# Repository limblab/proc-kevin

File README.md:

# proc-kevin
Kevin's analysis code

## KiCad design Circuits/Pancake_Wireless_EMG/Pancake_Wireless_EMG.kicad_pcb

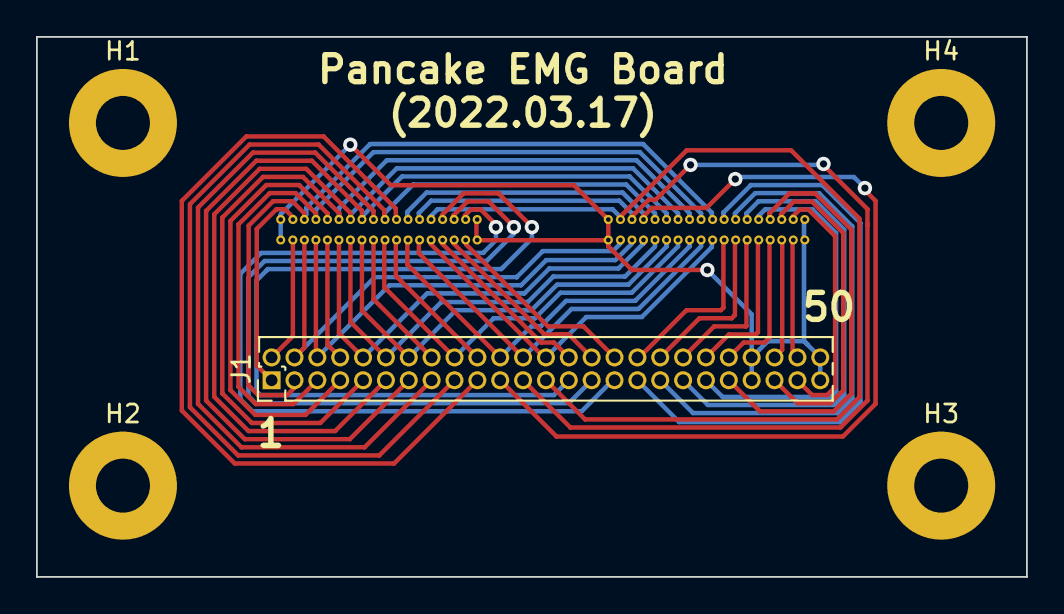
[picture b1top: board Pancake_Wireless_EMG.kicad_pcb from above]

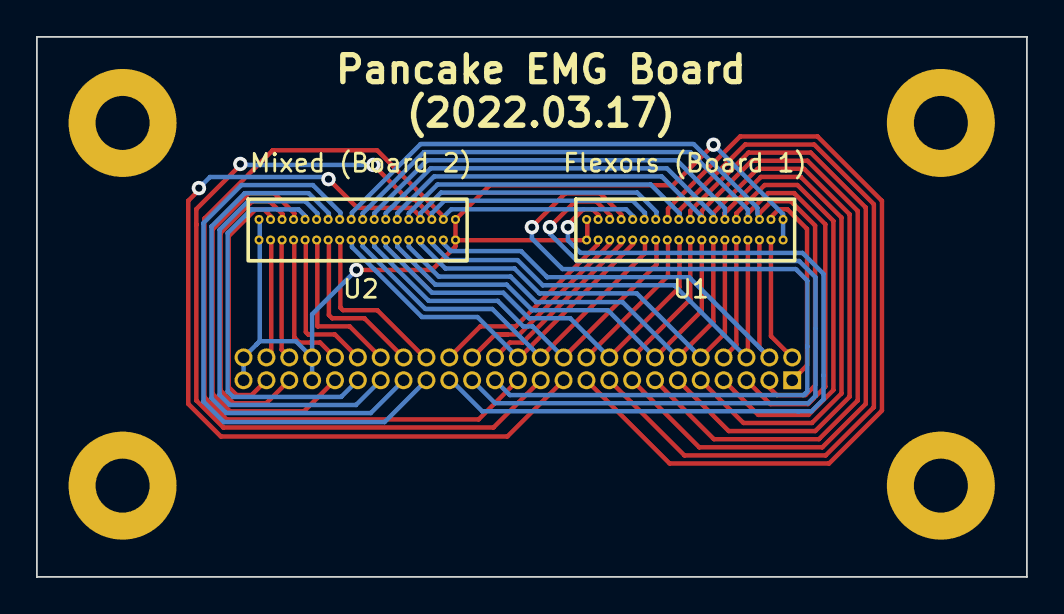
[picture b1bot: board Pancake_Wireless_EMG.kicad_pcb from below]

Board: 2 copper layers, 55.0 x 30.0 mm, 7 parts (2 on the bottom side), 47 nets.

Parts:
H1, H2, H3, H4: MountingHole; MountingHole_3mm_Pad
J1: Conn_02x25_Odd_Even; PinHeader_2x25_P1.27mm_Vertical
U1, U2: Omnetics_A79026; Omnetics_A97022

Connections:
/1DI_1: J1.27, U1.27 (In26)
/1DI_2: J1.28, U1.22 (In21)
/3DI_1: J1.31, U1.25 (In24)
/3DI_2: J1.32, U1.24 (In23)
/APB_1: J1.19, U1.31 (In30)
/APB_2: J1.20, U1.18 (In17)
/Bi_1: J1.47, U2.25 (In24)
/Bi_2: J1.48, U2.24 (In23)
/ECR_1: J1.36, U2.19 (In18)
/ECR_2: J1.37, U2.29 (In28)
/ECR_3: J1.38, U2.20 (In19)
/ECU_1: J1.33, U2.31 (In30)
/ECU_2: J1.34, U2.18 (In17)
/ECU_3: J1.35, U2.30 (In29)
/EDC1_1: J1.39, U2.28 (In27)
/EDC1_2: J1.40, U2.21 (In20)
/EDC2_1: J1.41, U2.27 (In26)
/EDC2_2: J1.42, U2.22 (In21)
/EPL_1: J1.25, U1.28 (In27), U2.8 (In7)
/EPL_2: J1.26, U1.21 (In20), U2.17 (In16)
/FCR1_1: J1.1, U1.8 (In7)
/FCR1_2: J1.2, U1.9 (In8)
/FCR2_1: J1.3, U1.7 (In6), U2.32 (In31)
/FCR2_2: J1.4, U1.10 (In9), U2.9 (In8)
/FCU1_1: J1.5, U1.6 (In5), U2.1 (In0)
/FCU1_2: J1.6, U1.11 (In10), U2.10 (In9)
/FCU2_1: J1.7, U1.5 (In4)
/FCU2_2: J1.8, U1.12 (In11)
/FDP1_1: J1.9, U1.4 (In3), U2.2 (In1)
/FDP1_2: J1.10, U1.13 (In12), U2.11 (In10)
/FDP2_1: J1.11, U1.3 (In2), U2.3 (In2)
/FDP2_2: J1.12, U1.14 (In13), U2.12 (In11)
/FDS1_1: J1.13, U1.2 (In1), U2.4 (In3)
/FDS1_2: J1.14, U1.15 (In14), U2.13 (In12)
/FDS2_1: J1.15, U1.1 (In0)
/FDS2_2: J1.16, U1.16 (In15)
/FPB_1: J1.21, U1.30 (In29), U2.6 (In5)
/FPB_2: J1.22, U1.19 (In18), U2.15 (In14)
/Gnd: J1.43, J1.44, J1.49, J1.50, U1.33 (GND), U1.34 (REF), U1.35 (REF), U1.36 (GND), U2.33 (GND), U2.34 (REF), U2.35 (REF), U2.36 (GND)
/Lum_1: J1.23, U1.29 (In28), U2.7 (In6)
/Lum_2: J1.24, U1.20 (In19), U2.16 (In15)
/PT_1: J1.17, U1.32 (In31), U2.5 (In4)
/PT_2: J1.18, U1.17 (In16), U2.14 (In13)
/Sup_1: J1.29, U1.26 (In25)
/Sup_2: J1.30, U1.23 (In22)
/Tri_1: J1.45, U2.26 (In25)
/Tri_2: J1.46, U2.23 (In22)

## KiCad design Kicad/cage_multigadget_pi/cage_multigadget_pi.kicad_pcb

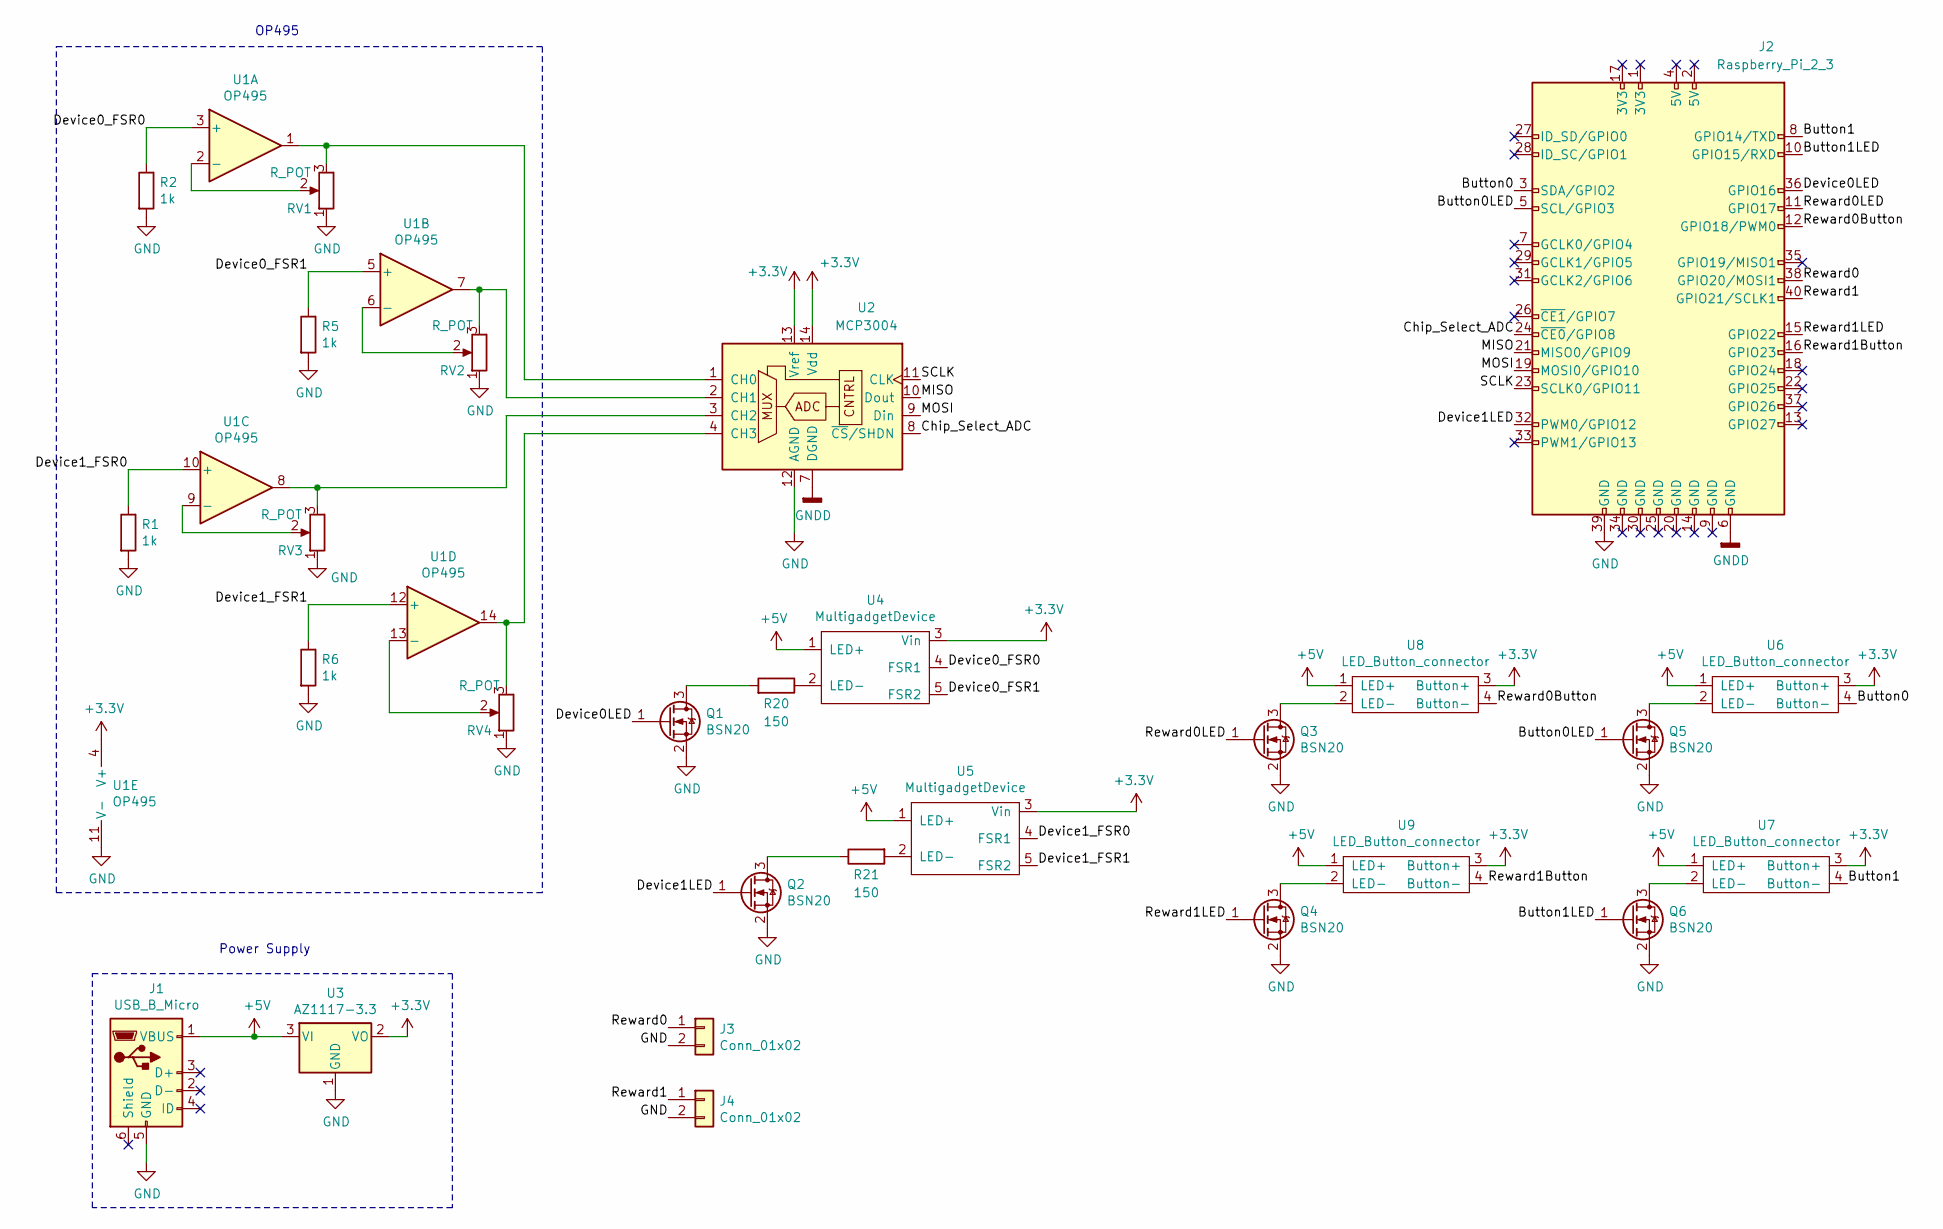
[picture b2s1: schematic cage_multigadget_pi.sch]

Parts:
J1: USB_B_Micro; USB_Micro_B_Female_10118194-0001LF
J2: Raspberry_Pi_2_3; Pin_Header_Straight_2x20_Pitch2.54mm
J3, J4: Conn_01x02; Socket_Strip_Straight_1x02_Pitch2.54mm
Q1, Q2, Q3, Q4, Q5, Q6: BSN20; SOT-23
R1, R2, R5, R6: 1k; R_1206_3216Metric_Pad1.42x1.75mm_HandSolder
R20, R21: 150; R_1206_3216Metric_Pad1.42x1.75mm_HandSolder
RV1, RV2, RV3, RV4: R_POT; Potentiometer_Trimmer_Bourns_3296Y
U1: OP495; DIP-14_W7.62mm
U2: MCP3004; DIP-14_W7.62mm
U3: AZ1117-3.3; SOT-223
U4, U5: MultigadgetDevice; CUI_MD-80S
U6, U7, U8, U9: LED_Button_connector; CUI_MD-80S

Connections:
+3V3: U1.4 (V+), U2.13 (Vref), U2.14 (Vdd), U3.2 (VO), U4.3 (Vin), U5.3 (Vin), U6.3 (Button+), U7.3 (Button+), U8.3 (Button+), U9.3 (Button+)
+5V: J1.1 (VBUS), U3.3 (VI), U4.1 (LED+), U5.1 (LED+), U6.1 (LED+), U7.1 (LED+), U8.1 (LED+), U9.1 (LED+)
/Button0: J2.3 (SDA/GPIO2), U6.4 (Button-)
/Button0LED: J2.5 (SCL/GPIO3), Q5.1 (G)
/Button1: J2.8 (GPIO14/TXD), U7.4 (Button-)
/Button1LED: J2.10 (GPIO15/RXD), Q6.1 (G)
/Chip_Select_ADC: J2.24 (~CE0~/GPIO8), U2.8 (~CS~/SHDN)
/Device0LED: J2.36 (GPIO16), Q1.1 (G)
/Device0_FSR0: R2.1, U1.3 (+), U4.4 (FSR1)
/Device0_FSR1: R5.1, U1.5 (+), U4.5 (FSR2)
/Device1LED: J2.32 (PWM0/GPIO12), Q2.1 (G)
/Device1_FSR0: R1.1, U1.10 (+), U5.4 (FSR1)
/Device1_FSR1: R6.1, U1.12 (+), U5.5 (FSR2)
/MISO: J2.21 (MISO0/GPIO9), U2.10 (Dout)
/MOSI: J2.19 (MOSI0/GPIO10), U2.9 (Din)
/Reward0: J2.38 (GPIO20/MOSI1), J3.1
/Reward0Button: J2.12 (GPIO18/PWM0), U8.4 (Button-)
/Reward0LED: J2.11 (GPIO17), Q3.1 (G)
/Reward1: J2.40 (GPIO21/SCLK1), J4.1
/Reward1Button: J2.16 (GPIO23), U9.4 (Button-)
/Reward1LED: J2.15 (GPIO22), Q4.1 (G)
/SCLK: J2.23 (SCLK0/GPIO11), U2.11 (CLK)
GND: J1.5 (GND), J2.39 (GND), J3.2, J4.2, Q1.2 (S), Q2.2 (S), Q3.2 (S), Q4.2 (S), Q5.2 (S), Q6.2 (S), R1.2, R2.2, R5.2, R6.2, RV1.1, RV2.1, RV3.1, RV4.1, U1.11 (V-), U2.12 (AGND), U3.1 (GND)
GNDD: J2.6 (GND), U2.7 (DGND)
unnamed: Q1.3 (D), R20.2
unnamed: Q2.3 (D), R21.1
unnamed: Q3.3 (D), U8.2 (LED-)
unnamed: Q4.3 (D), U9.2 (LED-)
unnamed: Q5.3 (D), U6.2 (LED-)
unnamed: Q6.3 (D), U7.2 (LED-)
unnamed: R20.1, U4.2 (LED-)
unnamed: R21.2, U5.2 (LED-)
unnamed: RV1.2, U1.2 (-)
unnamed: RV1.3, U1.1, U2.1 (CH0)
unnamed: RV2.2, U1.6 (-)
unnamed: RV2.3, U1.7, U2.2 (CH1)
unnamed: RV3.2, U1.9 (-)
unnamed: RV3.3, U1.8, U2.3 (CH2)
unnamed: RV4.2, U1.13 (-)
unnamed: RV4.3, U1.14, U2.4 (CH3)

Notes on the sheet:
Power Supply
OP495

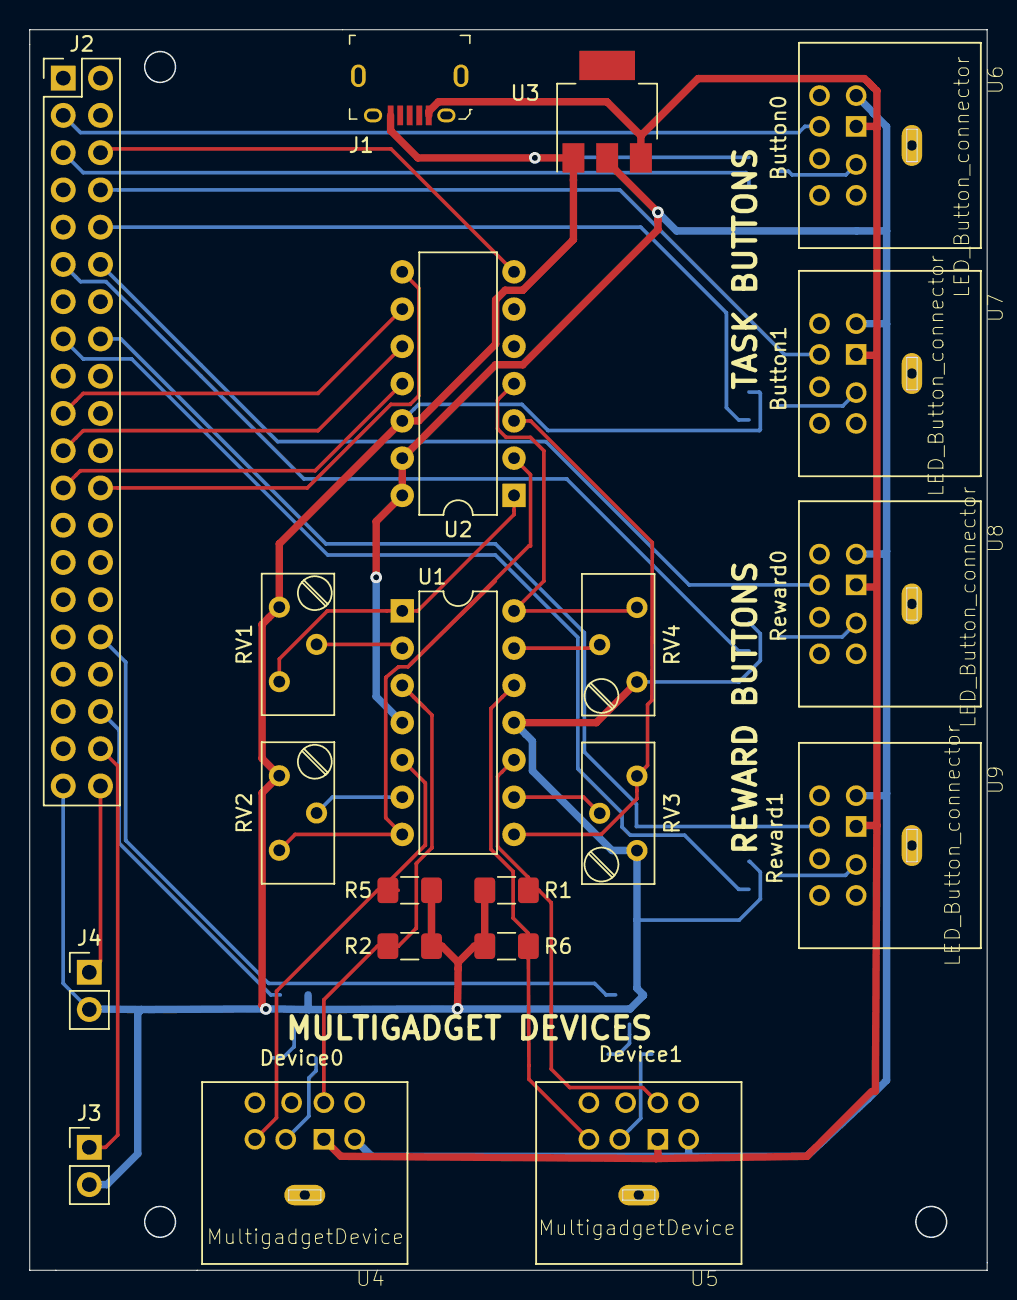
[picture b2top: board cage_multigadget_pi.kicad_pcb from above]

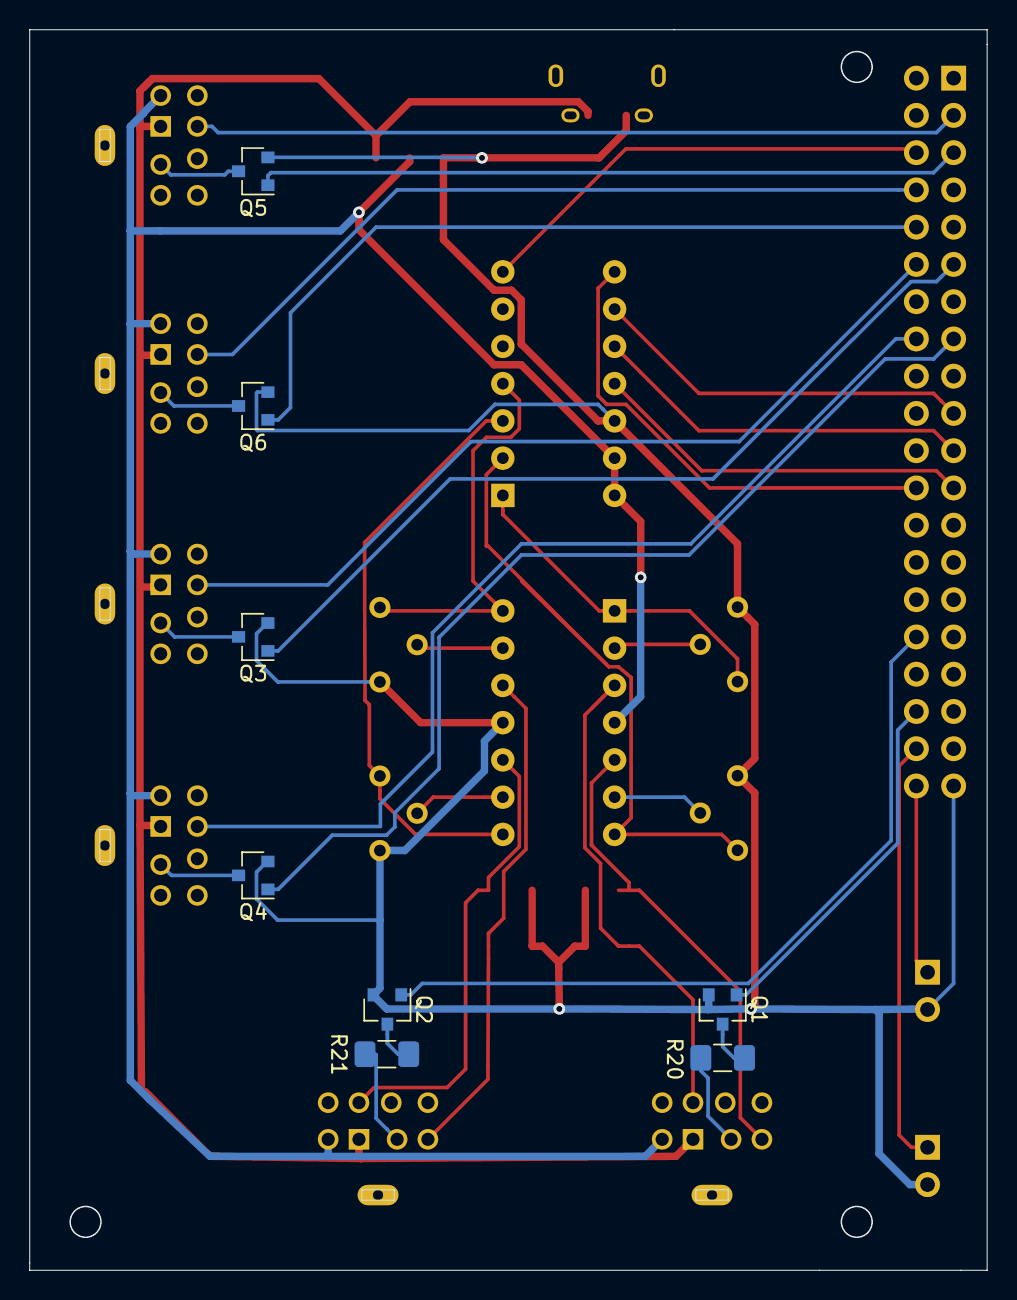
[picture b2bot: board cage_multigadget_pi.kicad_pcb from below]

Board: 2 copper layers, 65.3 x 84.6 mm, 29 parts (8 on the bottom side), 40 nets.

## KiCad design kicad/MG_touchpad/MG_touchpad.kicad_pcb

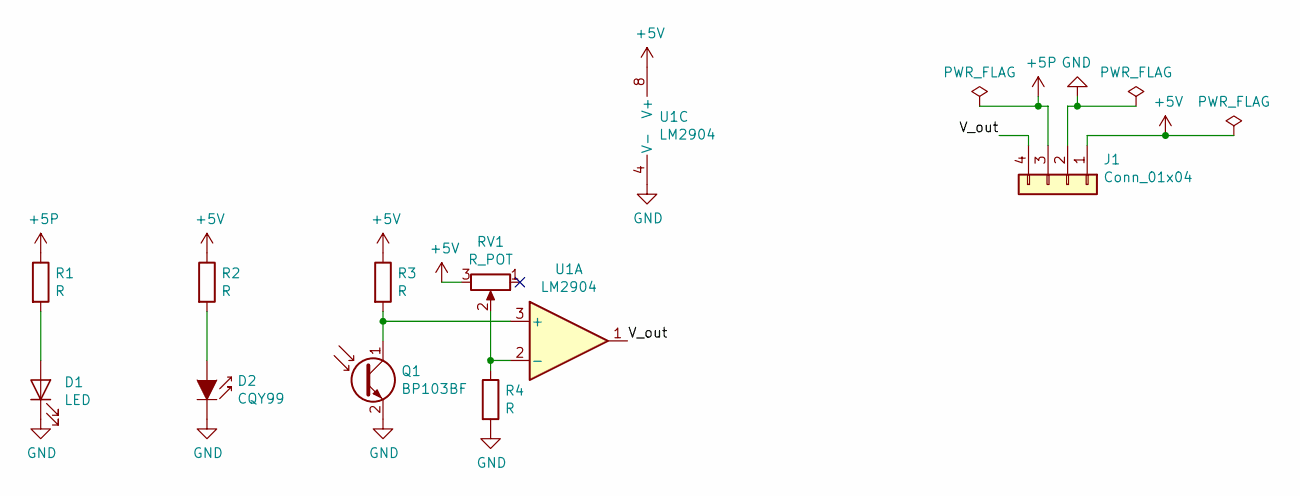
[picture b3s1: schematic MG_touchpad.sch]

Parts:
D1: LED; JST_PH_B2B-PH-K_02x2.00mm_Straight
D2: CQY99; JST_PH_B2B-PH-K_02x2.00mm_Straight
J1: Conn_01x04; Pin_Header_Angled_1x04_Pitch2.54mm
Q1: BP103BF; JST_PH_B2B-PH-K_02x2.00mm_Straight
R1, R2, R3, R4: R; R_1206
RV1: R_POT; Potentiometer_Trimmer_Bourns_3296Y
U1: LM2904; DIP-8_W7.62mm

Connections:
+5P: J1.3, R1.1
+5V: J1.1, R2.1, R3.1, RV1.3, U1.8 (V+)
/V_out: J1.4, U1.1
GND: D1.1 (K), D2.1 (K), J1.2, Q1.2 (E), R4.2, U1.4 (V-)
unnamed: D1.2 (A), R1.2
unnamed: D2.2 (A), R2.2
unnamed: Q1.1 (C), R3.2, U1.3 (+)
unnamed: R4.1, RV1.2, U1.2 (-)

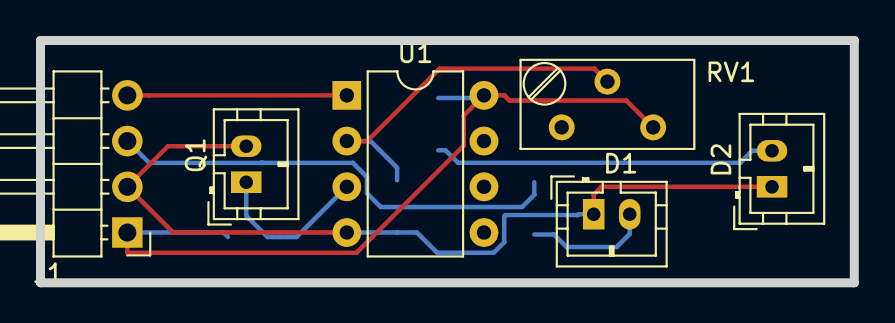
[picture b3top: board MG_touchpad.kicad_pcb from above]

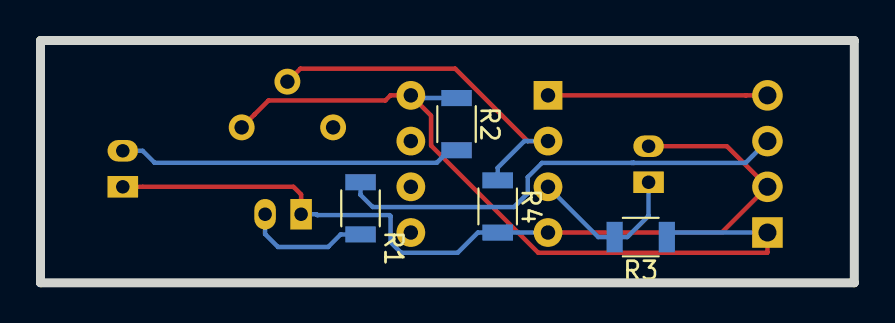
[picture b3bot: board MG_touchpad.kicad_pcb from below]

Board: 2 copper layers, 45.2 x 13.5 mm, 10 parts (4 on the bottom side), 8 nets.

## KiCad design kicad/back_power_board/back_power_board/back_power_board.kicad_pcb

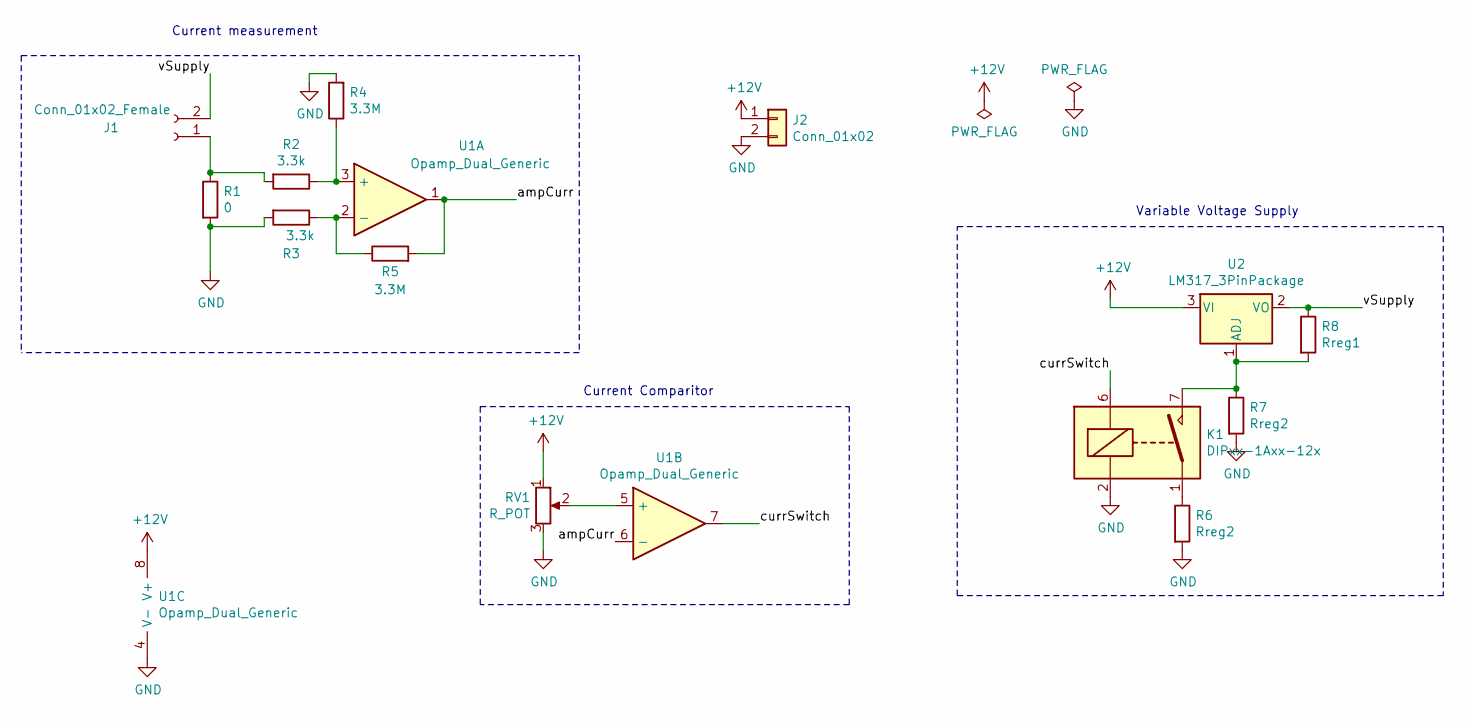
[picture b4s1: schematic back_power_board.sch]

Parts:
J1: Conn_01x02_Female; JST_PH_B2B-PH-K_02x2.00mm_Straight
J2: Conn_01x02; JST_PH_B2B-PH-K_02x2.00mm_Straight
K1: DIPxx-1Axx-12x; DIP-14_W3mm
R1: 0; R_Bare_Metal_Element_L16.3mm_W4.8mm_P15.30mm
R2, R3: 3.3k; R_1206_HandSoldering
R4, R5: 3.3M; R_1206_HandSoldering
R6, R7: Rreg2; R_Axial_DIN0207_L6.3mm_D2.5mm_P10.16mm_Horizontal
R8: Rreg1; R_Axial_DIN0207_L6.3mm_D2.5mm_P10.16mm_Horizontal
RV1: R_POT; Potentiometer_Trimmer_Bourns_3296Y
U1: Opamp_Dual_Generic; DIP-8_W7.62mm
U2: LM317_3PinPackage; TO-220-3_Horizontal

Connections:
+12V: J2.1, RV1.1, U1.8 (V+), U2.3 (VI)
/ampCurr: R5.2, U1.1, U1.6 (-)
/currSwitch: K1.6, U1.7
/vSupply: J1.2, R8.1, U2.2 (VO)
GND: J2.2, K1.2, K1.13, R1.2, R3.2, R4.2, R6.2, R7.2, RV1.3, U1.4 (V-)
unnamed: J1.1, R1.1, R2.2
unnamed: K1.1, K1.14, R6.1
unnamed: K1.7, K1.8, R7.1, R8.2, U2.1 (ADJ)
unnamed: R2.1, R4.1, U1.3 (+)
unnamed: R3.1, R5.1, U1.2 (-)
unnamed: RV1.2, U1.5 (+)

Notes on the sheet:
Current Comparitor
Current measurement
Variable Voltage Supply

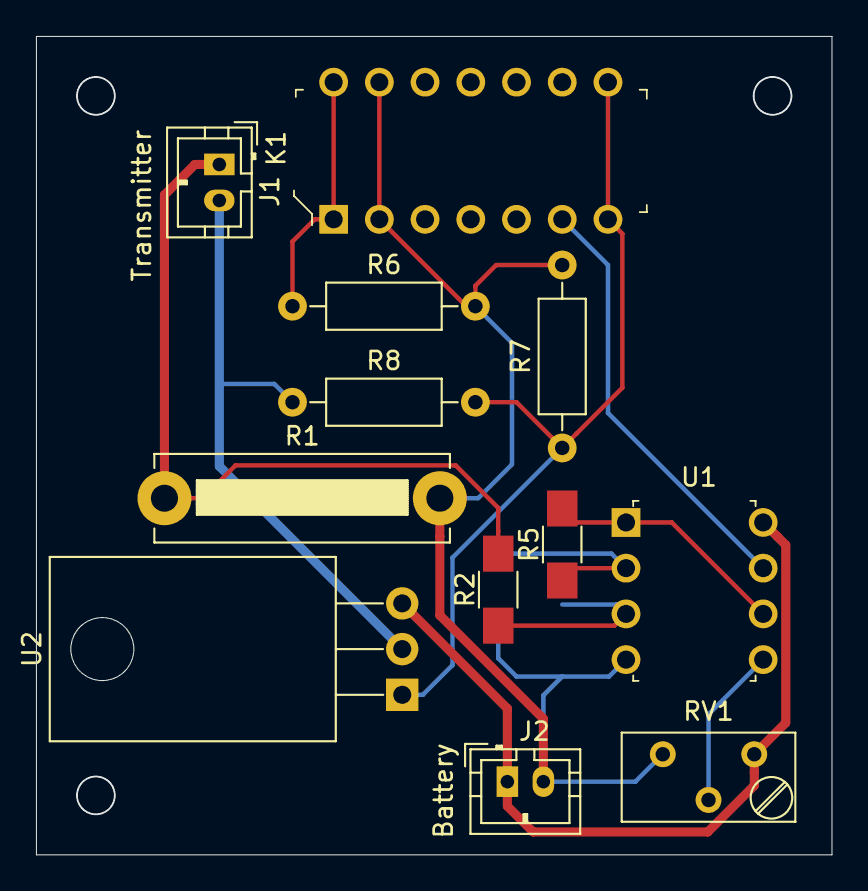
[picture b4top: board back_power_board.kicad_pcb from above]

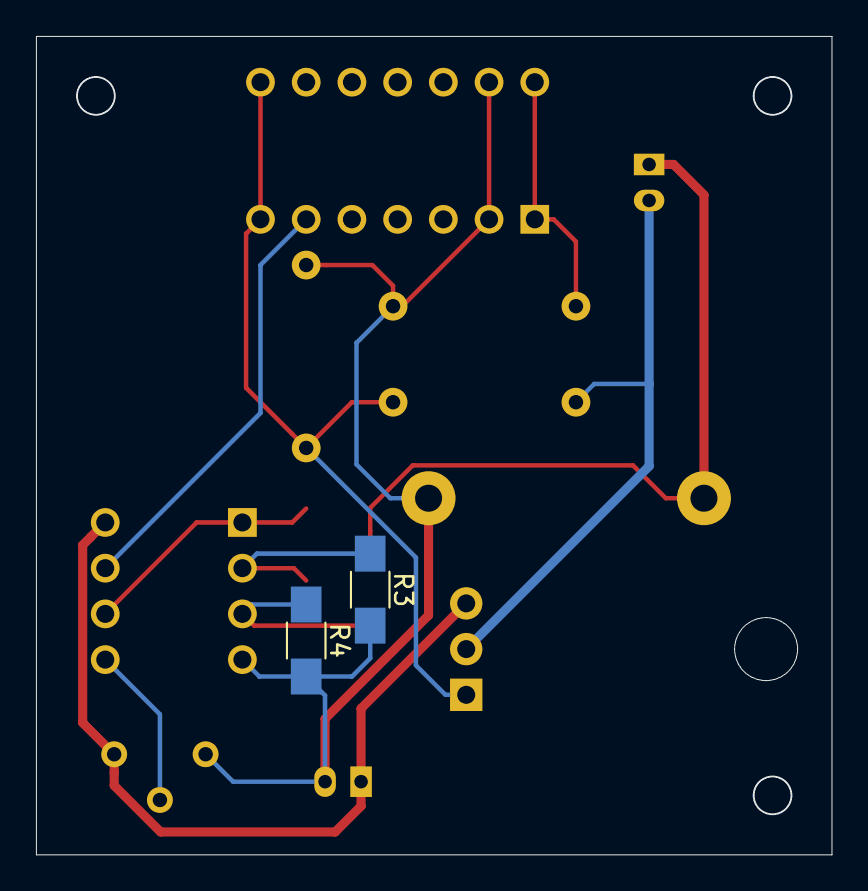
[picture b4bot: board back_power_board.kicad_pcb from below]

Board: 2 copper layers, 44.2 x 45.5 mm, 14 parts (2 on the bottom side), 11 nets.

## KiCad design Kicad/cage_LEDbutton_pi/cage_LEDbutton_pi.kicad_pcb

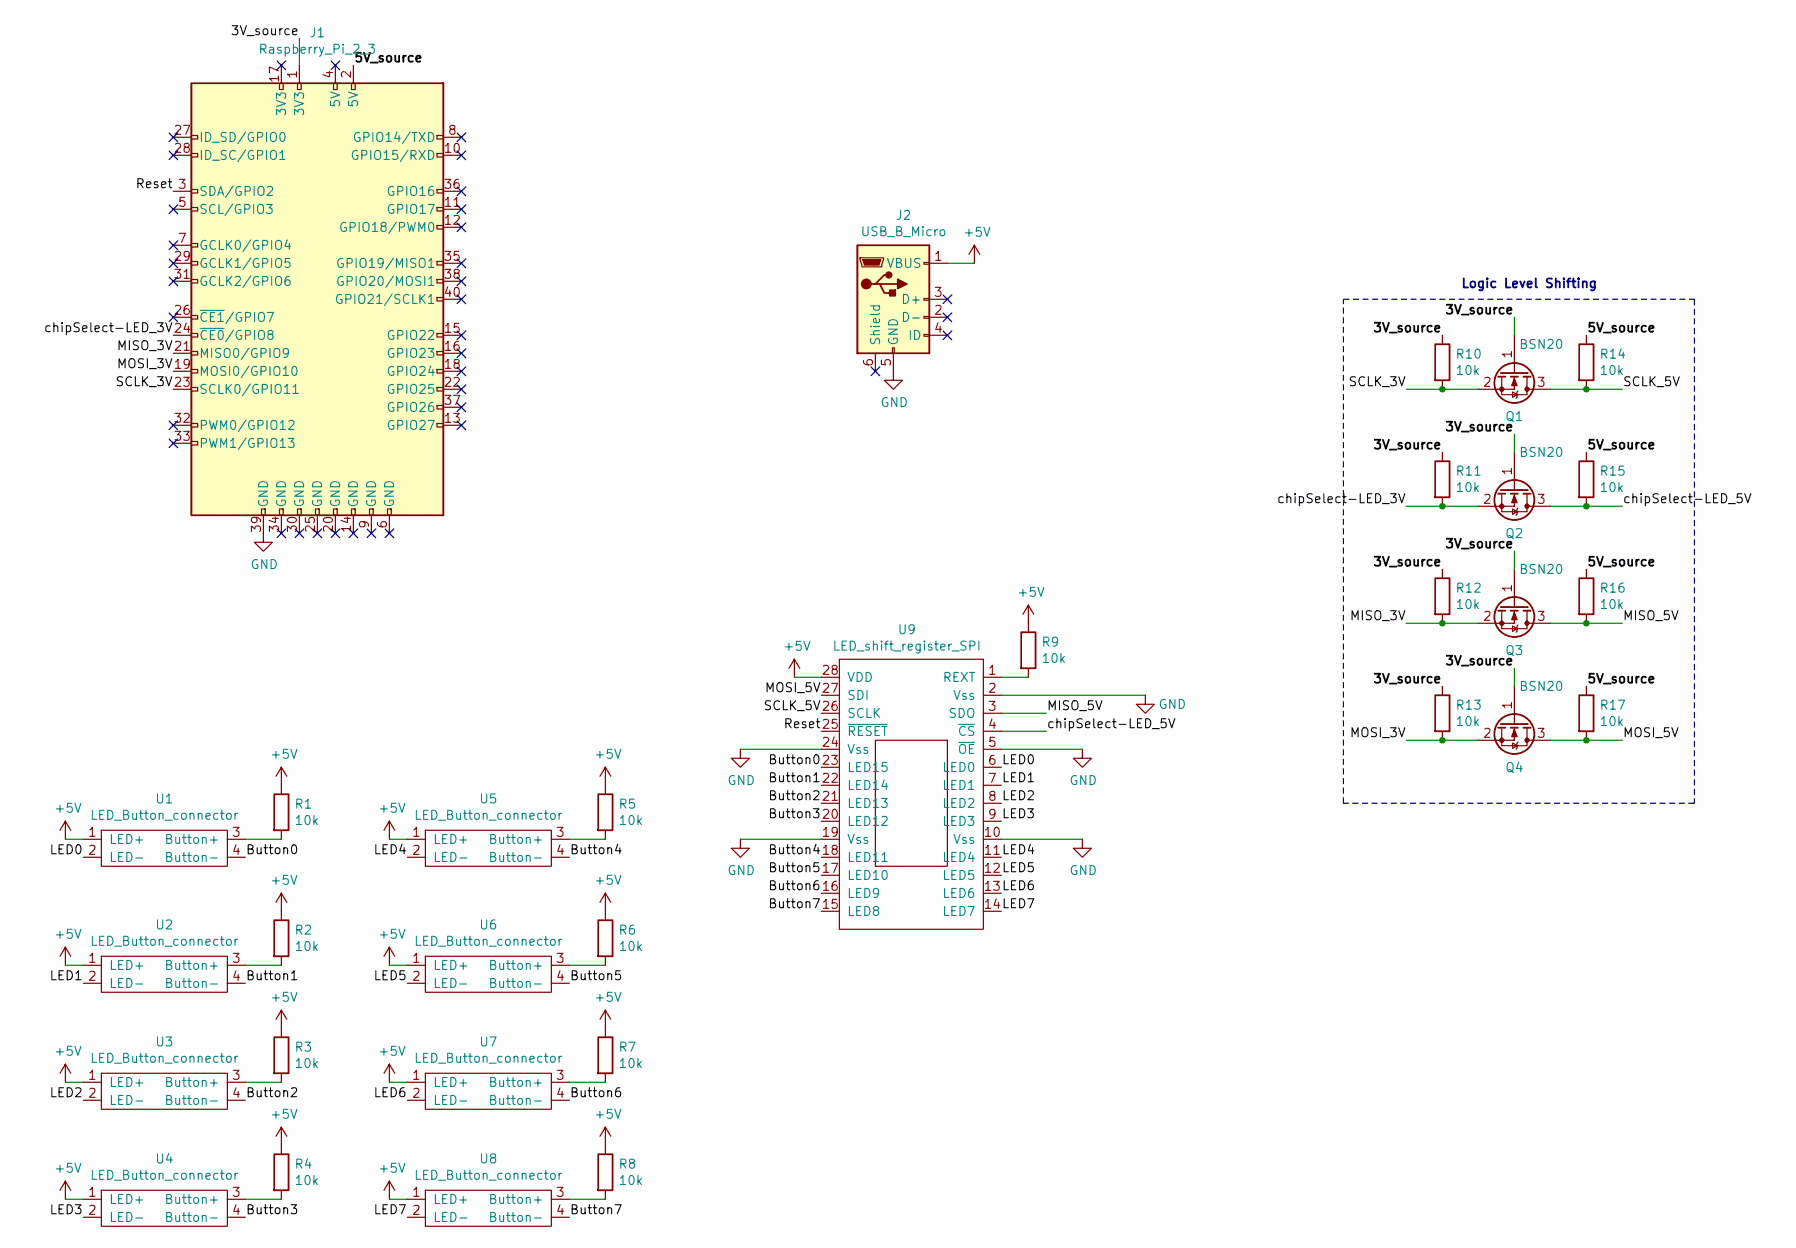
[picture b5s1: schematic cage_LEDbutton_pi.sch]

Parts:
J1: Raspberry_Pi_2_3; IDC-Header_2x20_P2.54mm_Vertical
J2: USB_B_Micro; USB_Micro-B_Amphenol_10103594-0001LF_Horizontal
Q1, Q2, Q3, Q4: BSN20; SOT-23
R1, R2, R3, R4, R5, R6, R7, R8, R9, R10, R11, R12, R13, R14, R15, R16, R17: 10k; R_1206_3216Metric_Pad1.42x1.75mm_HandSolder
U1, U2, U3, U4, U5, U6, U7, U8: LED_Button_connector; CUI_MD-80S
U9: LED_shift_register_SPI; HTSSOP-28-1EP_4.4x9.7mm_P0.65mm_EP3.4x9.5mm

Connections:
+5V: J2.1 (VBUS), R1.1, R2.1, R3.1, R4.1, R5.1, R6.1, R7.1, R8.1, R9.1, U1.1 (LED+), U2.1 (LED+), U3.1 (LED+), U4.1 (LED+), U5.1 (LED+), U6.1 (LED+), U7.1 (LED+), U8.1 (LED+), U9.28 (VDD)
/3V_source: J1.1 (3V3), Q1.1 (G), Q2.1 (G), Q3.1 (G), Q4.1 (G), R10.1, R11.1, R12.1, R13.1
/5V_source: J1.2 (5V), R14.1, R15.1, R16.1, R17.1
/Button0: U1.4 (Button-), U9.23 (LED15)
/Button1: U2.4 (Button-), U9.22 (LED14)
/Button2: U3.4 (Button-), U9.21 (LED13)
/Button3: U4.4 (Button-), U9.20 (LED12)
/Button4: U5.4 (Button-), U9.18 (LED11)
/Button5: U6.4 (Button-), U9.17 (LED10)
/Button6: U7.4 (Button-), U9.16 (LED9)
/Button7: U8.4 (Button-), U9.15 (LED8)
/LED0: U1.2 (LED-), U9.6 (LED0)
/LED1: U2.2 (LED-), U9.7 (LED1)
/LED2: U3.2 (LED-), U9.8 (LED2)
/LED3: U4.2 (LED-), U9.9 (LED3)
/LED4: U5.2 (LED-), U9.11 (LED4)
/LED5: U6.2 (LED-), U9.12 (LED5)
/LED6: U7.2 (LED-), U9.13 (LED6)
/LED7: U8.2 (LED-), U9.14 (LED7)
/MISO_3V: J1.21 (MISO0/GPIO9), Q3.2 (S), R12.2
/MISO_5V: Q3.3 (D), R16.2, U9.3 (SDO)
/MOSI_3V: J1.19 (MOSI0/GPIO10), Q4.2 (S), R13.2
/MOSI_5V: Q4.3 (D), R17.2, U9.27 (SDI)
/Reset: J1.3 (SDA/GPIO2), U9.25 (~RESET)
/SCLK_3V: J1.23 (SCLK0/GPIO11), Q1.2 (S), R10.2
/SCLK_5V: Q1.3 (D), R14.2, U9.26 (SCLK)
/chipSelect-LED_3V: J1.24 (~CE0~/GPIO8), Q2.2 (S), R11.2
/chipSelect-LED_5V: Q2.3 (D), R15.2, U9.4 (~CS)
GND: J1.39 (GND), J2.5 (GND), U9.2 (Vss), U9.5 (~OE), U9.10 (Vss), U9.19 (Vss), U9.24 (Vss)
unnamed: R1.2, U1.3 (Button+)
unnamed: R2.2, U2.3 (Button+)
unnamed: R3.2, U3.3 (Button+)
unnamed: R4.2, U4.3 (Button+)
unnamed: R5.2, U5.3 (Button+)
unnamed: R6.2, U6.3 (Button+)
unnamed: R7.2, U7.3 (Button+)
unnamed: R8.2, U8.3 (Button+)
unnamed: R9.2, U9.1 (REXT)

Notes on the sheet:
Logic Level Shifting

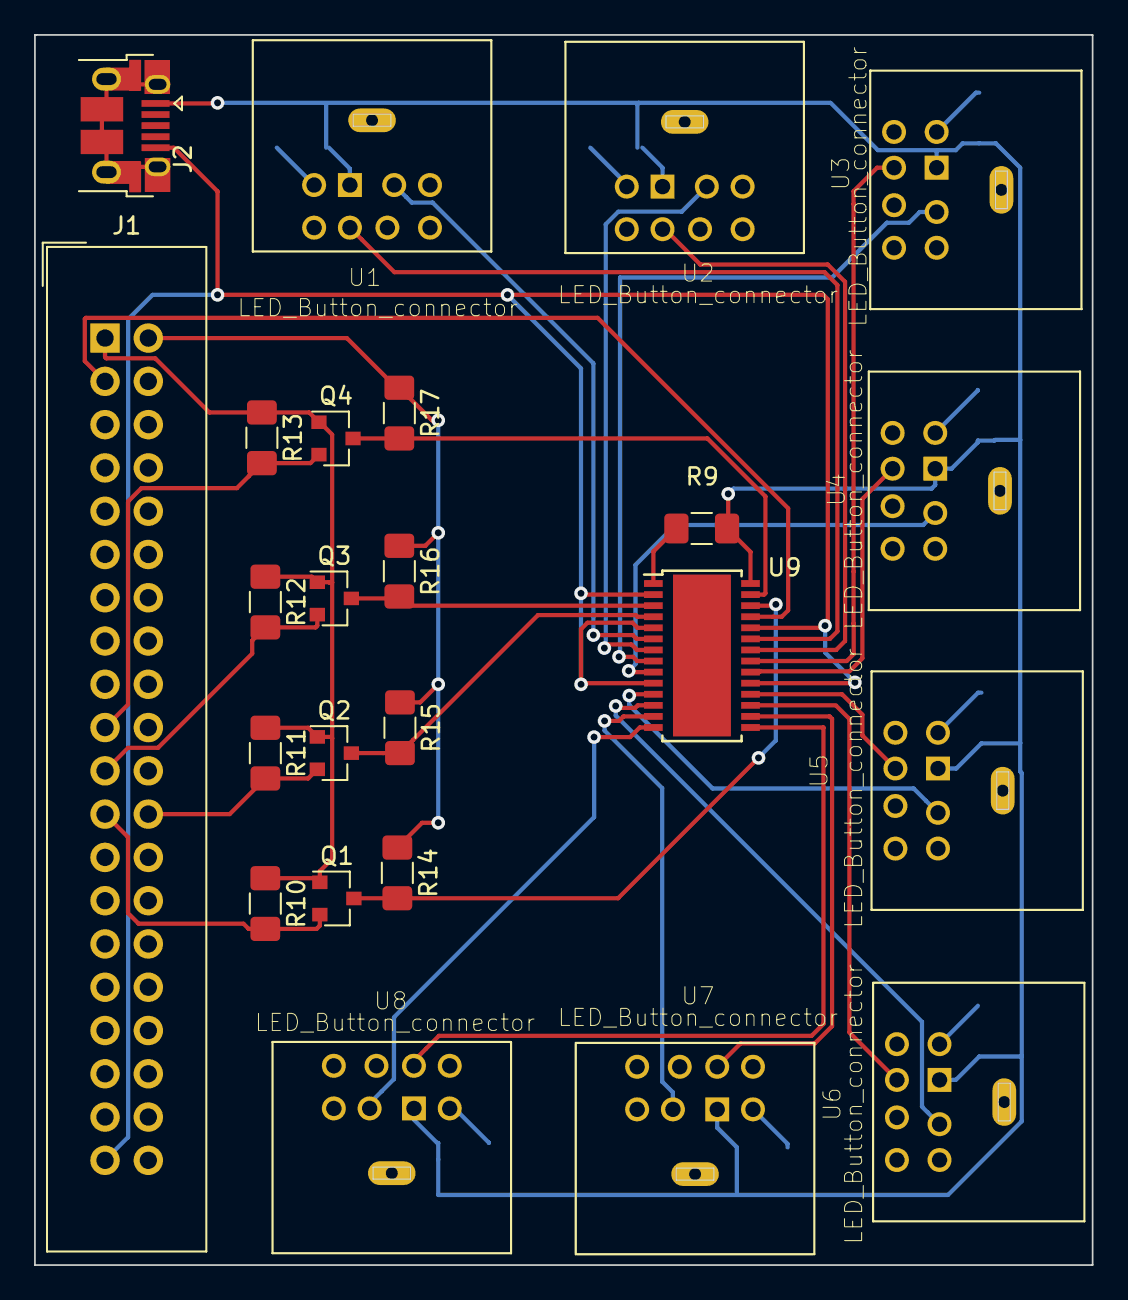
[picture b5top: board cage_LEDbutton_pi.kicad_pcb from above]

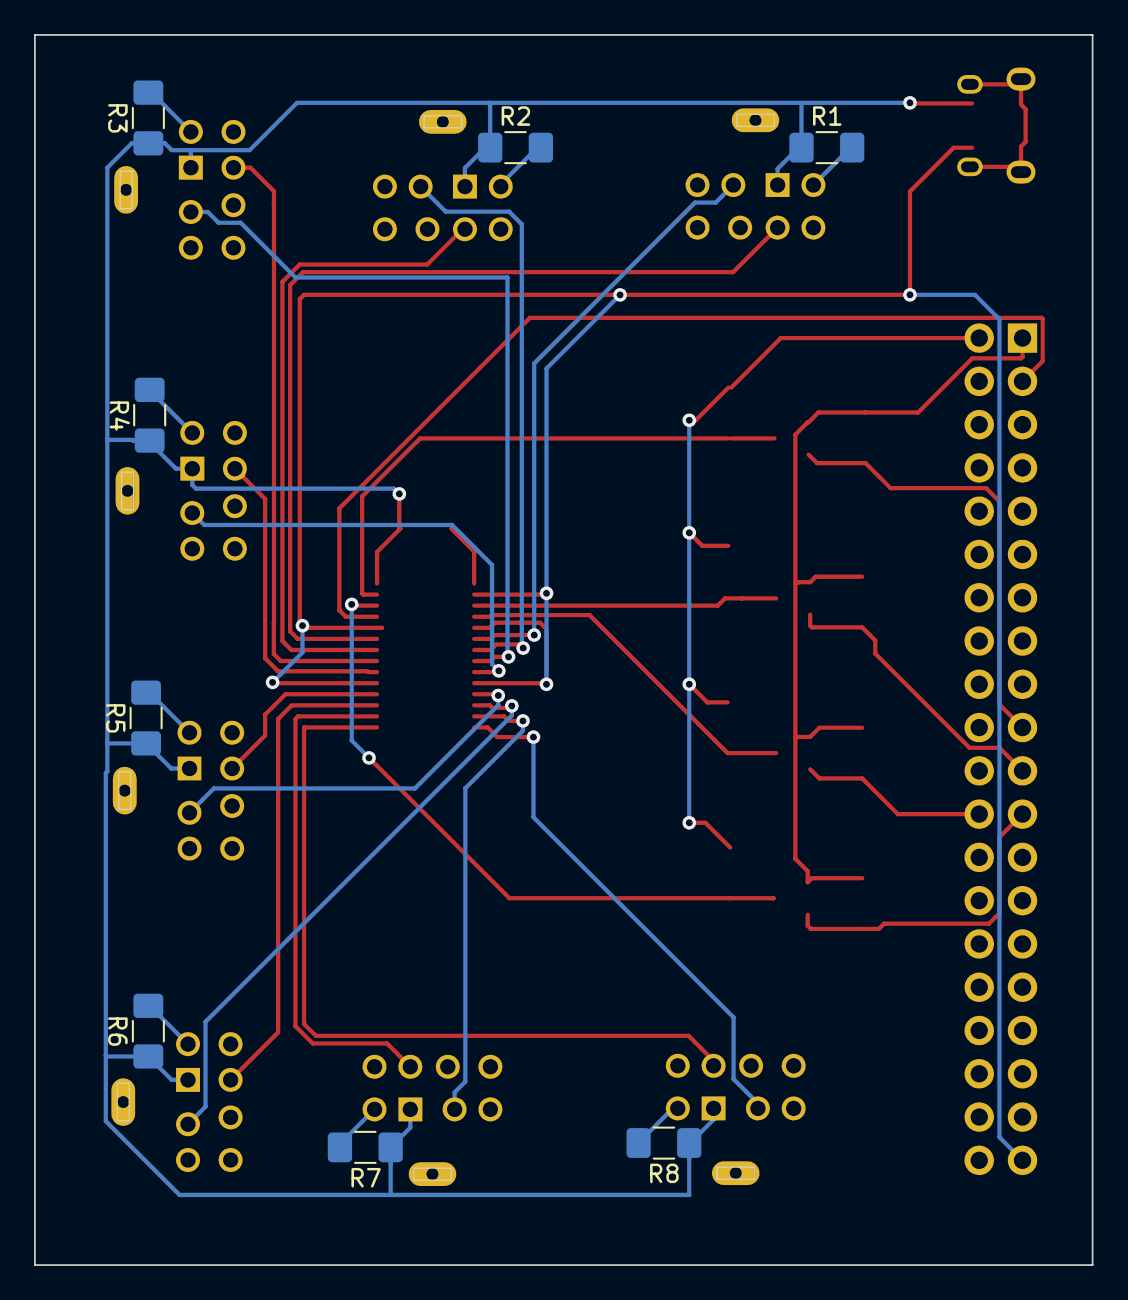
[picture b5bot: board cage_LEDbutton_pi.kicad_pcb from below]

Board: 2 copper layers, 62.1 x 72.2 mm, 32 parts (8 on the bottom side), 38 nets.

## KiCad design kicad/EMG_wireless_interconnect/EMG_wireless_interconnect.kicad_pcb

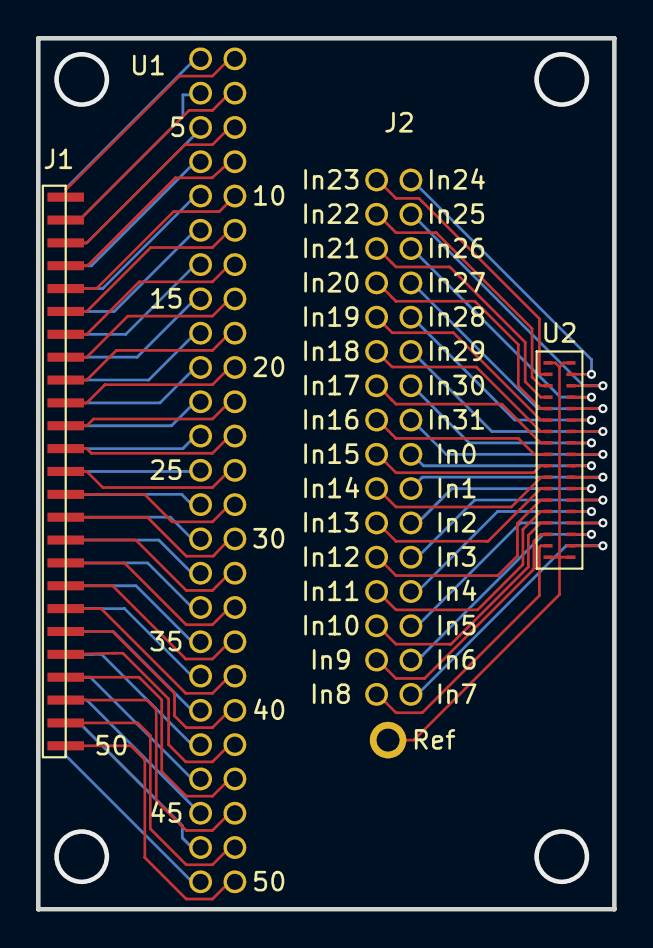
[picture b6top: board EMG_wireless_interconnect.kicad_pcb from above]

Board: 2 copper layers, 32.0 x 48.4 mm, 4 parts (0 on the bottom side), 83 nets.

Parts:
J1: Conn_02x25_Odd_Even; Samtec_edge
J2: Conn_01x33; Omnetics_xconn_point
U1: Conn_1x50; Samtec_xconn_point
U2: Omnetics_A79026

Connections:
/1: J1.1, U1.1
/2: J1.2, U1.2
/3: J1.3, U1.3
/4: J1.4, U1.4
/5: J1.5, U1.5
/6: J1.6, U1.6
/7: J1.7, U1.7
/8: J1.8, U1.8
/9: J1.9, U1.9
/10: J1.10, U1.10
/11: J1.11, U1.11
/12: J1.12, U1.12
/13: J1.13, U1.13
/14: J1.14, U1.14
/15: J1.15, U1.15
/16: J1.16, U1.16
/17: J1.17, U1.17
/18: J1.18, U1.18
/19: J1.19, U1.19
/20: J1.20, U1.20
/21: J1.21, U1.21
/22: J1.22, U1.22
/23: J1.23, U1.23
/24: J1.24, U1.24
/25: J1.25, U1.25
/26: J1.26, U1.26
/27: J1.27, U1.27
/28: J1.28, U1.28
/29: J1.29, U1.29
/30: J1.30, U1.30
/31: J1.31, U1.31
/32: J1.32, U1.32
/33: J1.33, U1.33
/34: J1.34, U1.34
/35: J1.35, U1.35
/36: J1.36, U1.36
/37: J1.37, U1.37
/38: J1.38, U1.38
/39: J1.39, U1.39
/40: J1.40, U1.40
/41: J1.41, U1.41
/42: J1.42, U1.42
/43: J1.43, U1.43
/44: J1.44, U1.44
/45: J1.45, U1.45
/46: J1.46, U1.46
/47: J1.47, U1.47
/48: J1.48, U1.48
/49: J1.49, U1.49
/50: J1.50, U1.50
/In_16: J2.17, U2.17
/In_17: J2.18, U2.18
/In_18: J2.19, U2.19
/In_19: J2.20, U2.20
/In_20: J2.21, U2.21
/In_21: J2.22, U2.22
/In_22: J2.23, U2.23
/In_23: J2.24, U2.24
/In_24: J2.25, U2.25
/In_25: J2.26, U2.26
/In_26: J2.27, U2.27
/In_27: J2.28, U2.28
/In_28: J2.29, U2.29
/In_29: J2.30, U2.30
/In_30: J2.31, U2.31
/In_31: J2.32, U2.32
/Ref: J2.33, U2.33, U2.34, U2.35, U2.36
unnamed: J2.1, U2.1
unnamed: J2.2, U2.2
unnamed: J2.3, U2.3
unnamed: J2.4, U2.4
unnamed: J2.5, U2.5
unnamed: J2.6, U2.6
unnamed: J2.7, U2.7
unnamed: J2.8, U2.8
unnamed: J2.9, U2.9
unnamed: J2.10, U2.10
unnamed: J2.11, U2.11
unnamed: J2.12, U2.12
unnamed: J2.13, U2.13
unnamed: J2.14, U2.14
unnamed: J2.15, U2.15
unnamed: J2.16, U2.16
